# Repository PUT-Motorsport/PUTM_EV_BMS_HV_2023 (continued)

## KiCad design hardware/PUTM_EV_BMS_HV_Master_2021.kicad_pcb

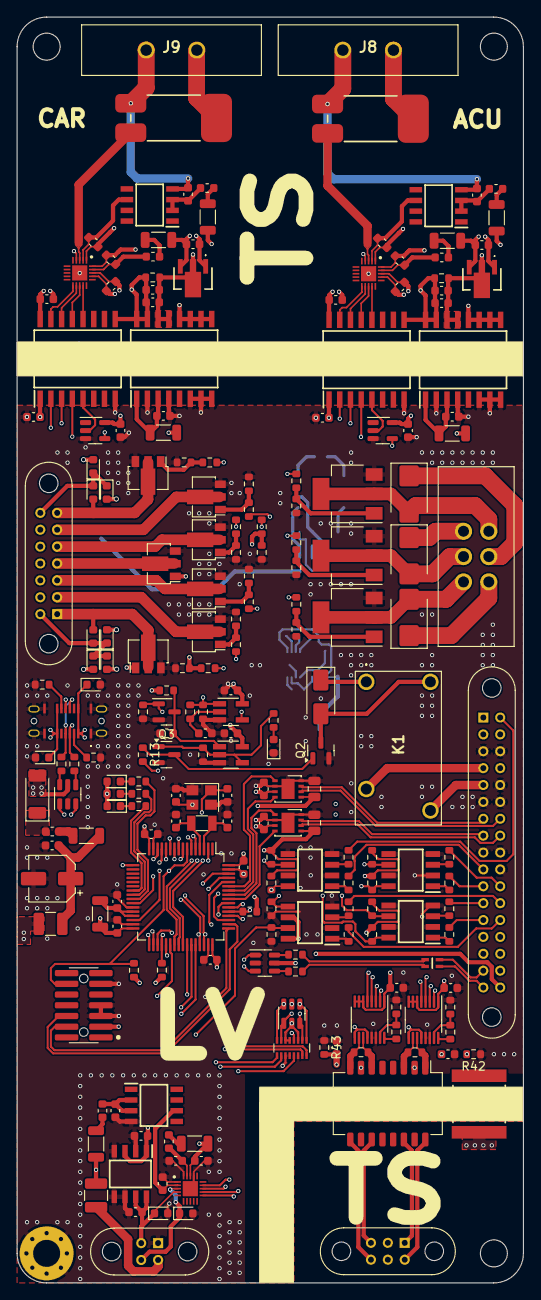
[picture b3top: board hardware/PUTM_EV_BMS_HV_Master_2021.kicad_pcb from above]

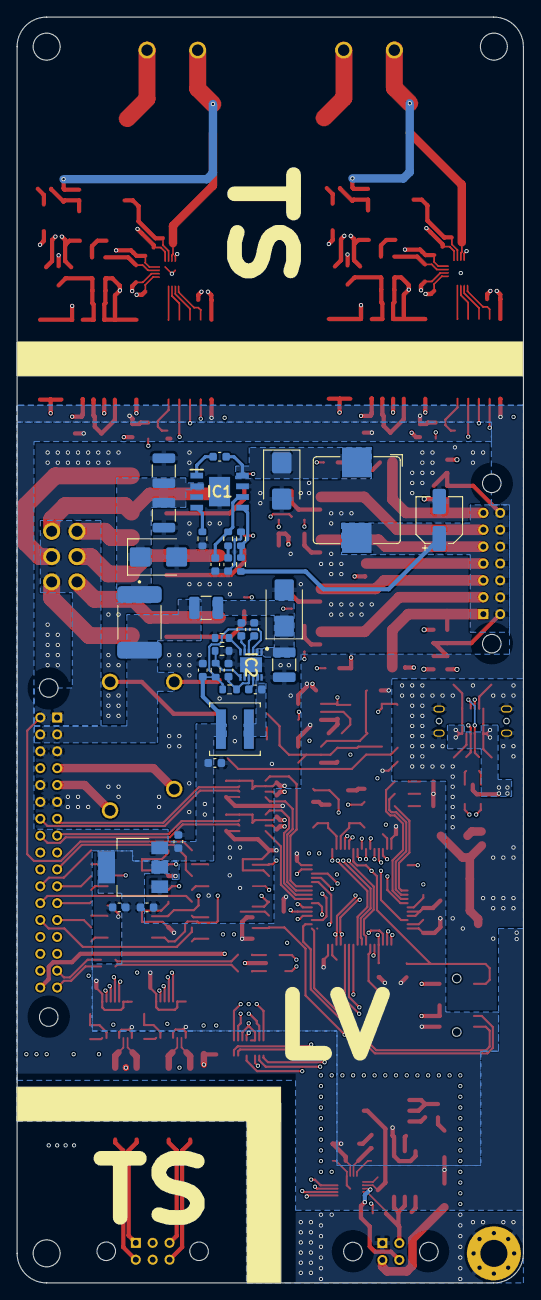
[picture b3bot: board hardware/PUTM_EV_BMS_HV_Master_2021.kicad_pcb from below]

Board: 4 copper layers, 60.0 x 150.0 mm, 253 parts (34 on the bottom side), 197 nets.

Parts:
C1, C2: 20pF; C_0603_1608Metric
C3, C4: 25pF; C_0603_1608Metric
C5, C6, C7, C8, C15, C16, C24, C25, C27, C28, C29, C33, C38, C39, C40, C42, C43, C46, C47, C49, C50, C52, C53, C56, C57, C58, C60, C61, C63, C64, C67, C68: 100nF; C_0603_1608Metric
C9, C10: 10uF/60V; C_1210_3225Metric
C11: 10pF; C_0603_1608Metric
C12: 12nF; C_0603_1608Metric
C13, C14: 1uF; C_0603_1608Metric
C17, C26: 100nF/60V; C_0603_1608Metric
C18: 100uF/12V; CP_Elec_5x4.5
C19: 47uF/12V; CP_Elec_5x4.5
C20: 2.2uF/60V; C_1210_3225Metric
C21: 5.6nF; C_0603_1608Metric
C22: 2.2uF; C_0603_1608Metric
C23, C41, C44, C51, C54, C55, C62, C65, C66: 10uF; C_0603_1608Metric
C30, C31: 47uF; C_0603_1608Metric
C32, C37: 100nF; C_0805_2012Metric
C34, C35: 22nF; C_0603_1608Metric
C36: 5.6nF/2000V; C2824
C45: 1nF; C_0603_1608Metric
C48, C59: 4.7uF; C_0603_1608Metric
D1, D2, D3, D8: SML-D12U1WT86; LED_0603_1608Metric
D4: SP0505BAHT; SOT-23-6
D5, D6, D17, D18, D19, D20, D21, D22, D23: CDBU0530; D_0603_1608Metric
D7: SS16-LTP; D_SMA
D9, D10, D15, D24: VSSB410S-E3/52T; D_SMB
D11, D16: SMBJ26CA-13-F; D_SMB
D12, D13: TSZU52C13; D_0603_1608Metric
D14: RB068LAM-30TFTR; D_SOD-128
F1, F3, F4: 0ZCH0050FF2G; Fuse_1210_3225Metric
F2: 576-2920L500/24SLDR; 2920L700SLPR
FB1, FB2, FB3, FB4, FB5, FB6, FB7: GZ1608D601TF; L_0603_1608Metric
FL1: DLW21SN501SK2L; DLW21SN121HQ2L
H1, H2, H4: M3; MountingHole_3.2mm_M3
H3: M3; MountingHole_3.2mm_M3_Pad_Via
IC1: RTQ2965GSP-QA; SOIC127P600X175-9N
IC2: MAX17643ATC+; SON50P300X300X80-13N
IC3: MCP3562T-E_NC; QFN40P300X300X60-21N-D
IC4: MCP1501-10E_SN; SOIC127P600X175-8N
IC5, IC10, IC16: REF193GSZ-REEL; SOIC127P600X175-8N
IC6, IC12: SN74LVC1G07DBVR; SOT-23-5
IC7, IC13: UCC12040DVE; SOIC127P1030X265-16N
IC8, IC14: ISO6763FDWR; SOIC127P1030X265-16N
IC9, IC15: AP7365-33YRG-13; AP736533YRG13
IC11, IC17: MCP3561T-E_NC; QFN40P300X300X60-21N-D
J1: M300-MV30645M1; M300MV30645M1
J2: M80-5103422; M80-51034YY
J3: M80-5100442; M80-51004YY
J4: FTSH-107-01-L-DV-K-A; FTSH-107-XX-YYY-DV-K-A
J5: M80-5101422; M80-51014YY
J6: USB4145-03-0070-C; USB4145030070C
J7: M80-5100622; M80-51006YY
J8, J9: M300-MV10345M1; M300MV10345M1
K1: 6-1419128-4; 614191284
L1, L3, L7, L10: 4.7uH; L_1206_3216Metric
L2: 33uH; L_Bourns_SRP1038C_10.0x10.0mm
L4: 10uH; L_Coilcraft_XAL5050-XXX
L5, L6, L8, L9, L11, L12: 1mH; L_1206_3216Metric
O1, O2, O3, O4: FOD8802DR2_IMG; SOIC127P600X175-8N
Q1, Q2, Q3: 2N7002; SOT-23
Q4, Q5, Q13: STN4NF06L; SOT-223-3_TabPin2
Q6, Q7, Q8, Q9, Q10, Q11, Q12: 2SK3065; SOT-89-3
R1, R2, R3, R5, R6, R15, R44, R45, R46, R47: 1k; R_0603_1608Metric
R4, R9, R11, R13, R14, R17, R19, R22, R23, R36, R37, R42, R43, R50, R51, R54, R55, R58, R59, R61, R64, R65, R67, R72, R73: 10k; R_0603_1608Metric
R7, R8: 5.1k; R_0603_1608Metric
R10: 100k; R_0603_1608Metric
R12: 1M; R_0603_1608Metric
R16, R18, R48, R49, R52, R53, R56, R57, R60, R66: 100R; R_0603_1608Metric
R20, R21, R34, R35, R62, R63, R70, R71: 2.7k; R_0603_1608Metric
R24: 20.5k; R_0603_1608Metric
R25: 392k; R_0603_1608Metric
R26: 147k; R_0603_1608Metric
R27: 10.5k; R_0603_1608Metric
R28: 40.2k; R_0603_1608Metric
R29: 4.7R; R_0603_1608Metric
R30: 105k; R_0603_1608Metric
R31: 23.2k; R_0603_1608Metric
R32, R33, R38, R39: 33R; R_0603_1608Metric
R40, R41: 120R; R_0603_1608Metric
R68, R69: 200R; R_0603_1608Metric
RD1, RD2: CDMM20M0F2500; CDMM
RN1: 33R; R_Array_Convex_8x0602
T1: HM1193NL; Transformer_Pulse_H1100NL
U1: STM32G484RETx; LQFP-64_10x10mm_P0.5mm
U2: 74LVC1G86; SOT-23-5_HandSoldering
U3: 74AUP1G32; SOT-23-5_HandSoldering
U4: LM1117-3.3; SOT-223-3_TabPin2
U5, U7: USBLC6-2SC6; SOT-23-6
U6, U8: MCP2542FD-E/MF; DFN-8-1EP_3x3mm_P0.65mm_EP1.55x2.4mm
U9, U10: LTC6820IMS; MSOP-16_3x4.039mm_P0.5mm
Y1: X322516MLB4SI; Crystal_SMD_3225-4Pin_3.2x2.5mm
Y2: Q13FC1350000400; Crystal_SMD_3215-2Pin_3.2x1.5mm

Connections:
+3.3VA: C23.1, L3.1, U1.28 (VREF+), U1.29 (VDDA)
+3V3: C6.2, C8.2, C14.1, C16.1, C24.1, C25.1, C28.1, C29.1, C32.2, C37.2, C39.1, C40.1, C42.1, C43.1, C47.1, C49.1, C58.1, C60.1, D1.2 (A), D2.2 (A), D3.2 (A), IC3.18 (DVDD), IC4.1 (VDD), IC4.3 (~SHDN), IC6.5, IC8.1 (VCC1), IC12.5, IC14.1 (VCC1), J4.3, L3.2, L5.1, O2.6, O2.8, R4.2, R5.2, R6.2, R12.1, R13.2, R22.2, R23.2, R64.2, R65.2, R72.2, R73.2, U1.16 (VDD), U1.32 (VDD), U1.48 (VDD), U1.64 (VDD), U2.5 (V), U3.5 (V), U4.2 (VO), U6.5 (VIO), U8.5 (VIO), U9.1 (EN), U9.6 (Vdds), U9.7 (POL), U9.8 (PHA), U9.9 (Vdd), U9.12 (MSTR), U10.1 (EN), U10.6 (Vdds), U10.7 (POL), U10.8 (PHA), U10.9 (Vdd), U10.12 (MSTR)
+5V: C13.1, C30.1, C31.1, C33.1, C38.1, F1.1, F3.1, IC2.3 (~RESET), L4.2, L6.1, L7.1, L10.1, R29.2, R30.2, U4.3 (VI), U6.3 (VDD), U8.3 (VDD)
+12V: C19.1, D17.1 (K), D18.1 (K), D19.1 (K), D20.1 (K), D21.1 (K), D22.1 (K), D23.1 (K), J5.8, J5.9, J5.10, J5.11, J5.12, J5.13, J5.14, L2.2, R26.2
/AIR_M_DETECT: O3.8, R64.1, U1.26 (PB2)
/AIR_PRE_DETECT: O3.6, R65.1, U1.17 (PA3)
/AIR_P_DETECT: O1.6, R23.1, U1.30 (PB10)
/AMS_FAULT_MCU: R9.2, R10.2, U1.51 (PA15), U2.1
/BOOT: O2.5, R36.2, U1.61 (PB8)
/CHARGER_DETECT: O4.8, R72.1, U1.62 (PB9)
/CLK_IN: C2.1, U1.5 (PF0), Y1.1
/CLK_OUT: C1.2, U1.6 (PF1), Y1.3
/Communication/LTC_1_I+: R40.2, T1.1, U9.11 (IP)
/Communication/LTC_1_I-: R40.1, T1.3, U9.10 (IM)
/Communication/LTC_1_OUT_I+: J7.4, T1.16
/Communication/LTC_1_OUT_I-: J7.1, T1.14
/Communication/LTC_2_I+: R41.2, T1.6, U10.11 (IP)
/Communication/LTC_2_I-: R41.1, T1.8, U10.10 (IM)
/Communication/LTC_2_OUT_I+: J7.3, T1.11
/Communication/LTC_2_OUT_I-: J7.6, T1.9
/Communication/LTC_CHASSIS: C36.2, J7.2, J7.5
/Connectors/MISO_C: D4.4 (K), J2.33, RN1.9 (R8.2)
/Connectors/MOSI_C: D4.3 (K), J2.32, RN1.10 (R7.2)
/Connectors/SCK_C: D4.5 (K), J2.31, RN1.12 (R5.2)
/Connectors/~EXT_CS_I_C: D4.6 (K), J2.14, RN1.16 (R1.2)
/Connectors/~EXT_CS_V_C: D4.1 (K), J2.15, RN1.15 (R2.2)
/FAN_1_CTRL: R48.2, U1.14 (PA2)
/FAN_2_CTRL: R52.2, U1.13 (PA1)
/FAN_3_CTRL: R56.2, U1.12 (PA0)
/FAN_4_CTRL: R60.2, U1.11 (PC3)
/FAN_5_CTRL: R49.2, U1.10 (PC2)
/FAN_6_CTRL: R53.2, U1.9 (PC1)
/FAN_7_CTRL: R57.2, U1.8 (PC0)
/IMD_SENS_PWM: O2.7, R37.1, U1.38 (PC6)
/LTC_1_~CS: U1.34 (PB12), U9.5 (~CS)
/LTC_2_~CS: U1.33 (PB11), U10.5 (~CS)
/LTC_MISO: R6.1, U1.36 (PB14), U9.3 (MISO), U10.3 (MISO)
/LTC_MOSI: U1.37 (PB15), U9.2 (MOSI), U10.2 (MOSI)
/LTC_SCK: U1.35 (PB13), U9.4 (SCK), U10.4 (SCK)
/MCU_CANFD1_RX: U1.58 (PB5), U8.4 (RXD)
/MCU_CANFD1_TX: U1.59 (PB6), U8.1 (TXD)
/MCU_CANFD2_RX: U1.56 (PB3), U6.4 (RXD)
/MCU_CANFD2_TX: U1.57 (PB4), U6.1 (TXD)
/MCU_D+: U1.46 (PA12), U5.3 (I/O2), U7.3 (I/O2)
/MCU_D-: U1.45 (PA11), U5.1 (I/O1), U7.1 (I/O1)
/MCU_LED_1: R3.1, U1.23 (PC5)
/MCU_LED_2: R2.1, U1.24 (PB0)
/MCU_LED_3: R1.1, U1.25 (PB1)
/Measurements/3V_REF: C46.2, IC3.2 (REFIN+), IC5.6 (REF_OUT)
/Measurements/Isolated acu measurement/3V_REF: C56.2, IC10.6 (REF_OUT), IC11.2 (REFIN+)
/Measurements/Isolated acu measurement/HV_+3.3V: C50.1, C53.1, C57.1, IC8.16 (VCC2), IC9.3 (VO), IC11.18 (DVDD), L9.1
/Measurements/Isolated acu measurement/HV_+5V: C51.1, C52.2, IC7.13 (SEL), IC7.14 (VISO), IC9.2 (VI), L8.1, R68.2
/Measurements/Isolated acu measurement/HV_GND: C50.2, C51.2, C52.1, C53.2, C54.2, C55.2, C56.1, C57.2, IC7.9 (GNDS), IC7.10 (NCS), IC7.11 (NCS), IC7.12 (NCS), IC7.15 (GNDS), IC7.16 (GNDS), IC8.9 (GND2), IC9.1 (GND), IC10.4 (GND), IC11.1 (REFIN-), IC11.4 (CH1), IC11.17 (DGND), IC11.20 (AGND), IC11.21 (EP), J8.1, R68.1, RD1.2
/Measurements/Isolated acu measurement/HV_MES+: IC11.3 (CH0), RD1.3
/Measurements/Isolated acu measurement/HV_SCK: IC8.14 (OUTB), IC11.12 (SCK)
/Measurements/Isolated acu measurement/HV_SDI: IC8.13 (OUTC), IC11.13 (SDI)
/Measurements/Isolated acu measurement/HV_SDO: IC8.12 (IND), IC11.14 (SDO)
/Measurements/Isolated acu measurement/HV_~CS: IC8.15 (OUTA), IC11.11 (~CS)
/Measurements/Isolated car measurement/3V_REF: C67.2, IC16.6 (REF_OUT), IC17.2 (REFIN+)
/Measurements/Isolated car measurement/HV_+3.3V: C61.1, C64.1, C68.1, IC14.16 (VCC2), IC15.3 (VO), IC17.18 (DVDD), L12.1
/Measurements/Isolated car measurement/HV_+5V: C62.1, C63.2, IC13.13 (SEL), IC13.14 (VISO), IC15.2 (VI), L11.1, R69.2
/Measurements/Isolated car measurement/HV_GND: C61.2, C62.2, C63.1, C64.2, C65.2, C66.2, C67.1, C68.2, IC13.9 (GNDS), IC13.10 (NCS), IC13.11 (NCS), IC13.12 (NCS), IC13.15 (GNDS), IC13.16 (GNDS), IC14.9 (GND2), IC15.1 (GND), IC16.4 (GND), IC17.1 (REFIN-), IC17.4 (CH1), IC17.17 (DGND), IC17.20 (AGND), IC17.21 (EP), J9.1, R69.1, RD2.2
/Measurements/Isolated car measurement/HV_MES+: IC17.3 (CH0), RD2.3
/Measurements/Isolated car measurement/HV_SCK: IC14.14 (OUTB), IC17.12 (SCK)
/Measurements/Isolated car measurement/HV_SDI: IC14.13 (OUTC), IC17.13 (SDI)
/Measurements/Isolated car measurement/HV_SDO: IC14.12 (IND), IC17.14 (SDO)
/Measurements/Isolated car measurement/HV_~CS: IC14.15 (OUTA), IC17.11 (~CS)
/Power/5V_SW: C20.1, D16.1 (K), F4.1, IC2.1 (VIN), IC2.2 (EN/UVLO)
/Power/12V_SW: C17.2, D15.1 (K), IC1.8 (SW), L2.1
/Power/12V_VIN: C9.1, C10.1, D11.1 (K), F2.1, IC1.2 (VIN)
/RTC_CLK_IN: C3.2, U1.3 (PC14), Y2.2
/RTC_CLK_OUT: C4.1, U1.4 (PC15), Y2.1
/SAFETY_DETECT: O4.6, R73.1, U1.2 (PC13)
/SIGNAL_AIR_M: R16.2, U1.41 (PC9)
/SIGNAL_AIR_P: R66.2, U1.40 (PC8)
/SIGNAL_AIR_PRE: R18.2, U1.39 (PC7)
/Safeties and related/AMS_FAULT: Q3.1 (G), R14.2, R15.1, U3.2, U3.4
/Safeties and related/AMS_FAULT_INTER: Q2.1 (G), Q3.3 (D), R13.1
/Safeties and related/CAP_VOLT: C7.2, Q1.3 (D), R12.2, U3.1
/Safeties and related/EDGE_DETECT: Q1.1 (G), R11.1, U2.4
/Safeties and related/IN_DELAY: C5.2, R10.1, U2.2
/Safeties and related/RELAY-: D7.2 (A), K1.4, Q2.3 (D)
/~MES_ACU_CS: IC8.2 (INA), U1.60 (PB7)
/~MES_CAR_CS: IC14.2 (INA), U1.55 (PD2)
/~SENS_CS: IC3.11 (~CS), U1.42 (PA8)
AIR_M-: D9.2 (A), J1.3, Q4.2 (D)
AIR_M_DETECTION: J2.13, R62.2
AIR_P-: D24.2 (A), J1.5, Q13.2 (D)
AIR_PRE-: D10.2 (A), J1.4, Q5.2 (D)
AIR_PRE_DETECTION: J2.12, R63.2
AIR_P_DETECTION: J2.28, R21.2
AMS_SAFETY_1: J2.4, K1.2
AMS_SAFETY_2: J2.5, K1.3
BOOT0: J2.29, R35.2
CANFD1+: J2.7, U8.7 (CANH)
CANFD1-: J2.24, U8.6 (CANL)
CANFD2+: J2.8, U6.7 (CANH)
CANFD2-: J2.25, U6.6 (CANL)
CHARGER_DETECTION: J2.10, R70.2
CUR_SENS_REF: C45.2, D5.1 (K), IC3.4 (CH1), IC4.7 (OUT), IC4.8 (FB), J3.2
CUR_SENS_SIG: D6.1 (K), IC3.3 (CH0), J3.4
D+: J6.A6 (D+), J6.B6 (D+), R32.2
D-: J6.A7 (D-), J6.B7 (D-), R33.1
EXT_RESET: J2.11, R20.2
EX_D+: FL1.4, J2.17
EX_D-: FL1.1, J2.16
EX_VBUS: J2.34, U7.5 (VBUS)
FAN1-: D17.2 (A), J5.1, Q6.2 (D)
FAN2-: D19.2 (A), J5.2, Q8.2 (D)
FAN3-: D21.2 (A), J5.3, Q10.2 (D)
FAN4-: D23.2 (A), J5.4, Q12.2 (D)
FAN5-: D18.2 (A), J5.5, Q7.2 (D)
FAN6-: D20.2 (A), J5.6, Q9.2 (D)
FAN7-: D22.2 (A), J5.7, Q11.2 (D)
GND: C1.1, C2.2, C3.1, C4.2, C5.1, C6.1, C7.1, C8.1, C9.2, C10.2, C11.2, C12.2, C13.2, C14.2, C15.2, C16.2, C18.2, C19.2, C20.2, C21.2, C22.2, C23.2, C24.2, C25.2, C27.2, C28.2, C29.2, C30.2, C31.2, C32.1, C33.2, C34.2, C35.2, C36.1, C37.1, C38.2, C39.2, C40.2, C41.2, C42.2, C43.2, C44.2, C45.1, C46.1, C47.2, C48.2, C49.2, C58.2, C59.2, C60.2, D4.2 (A), D5.2 (A), D6.2 (A), D8.1 (K), D11.2 (A), D12.2 (A), D13.2 (A), D15.2 (A), D16.2 (A), H3.1, IC1.7 (GND), IC1.9 (EP), IC2.8 (GND), IC2.12 (PGND), IC2.13 (EP), IC3.1 (REFIN-), IC3.17 (DGND), IC3.20 (AGND), IC3.21 (EP), IC4.2 (GND), IC4.4 (GND), IC4.5 (GND), IC4.6 (GND), IC5.4 (GND), IC6.3, IC7.2 (GNDP), IC7.4 (SYNC), IC7.6 (NC), IC7.7 (NC), IC7.8 (NC), IC8.8 (GND1), IC12.3, IC13.2 (GNDP), IC13.4 (SYNC), IC13.6 (NC), IC13.7 (NC), IC13.8 (NC), IC14.8 (GND1), J2.3, J2.6, J2.9, J2.20, J2.22, J2.23, J2.26, J2.27, J3.1, J4.5, J4.7, J4.11, J6.A1 (GND), J6.A12 (GND), J6.B1 (GND), J6.B12 (GND), J6.MH (SHIELD), O1.2, O1.4, O1.5, O1.7, O2.2, O2.4, O3.2, O3.4, O3.5, O3.7, O4.2, O4.4, O4.5, O4.7, Q1.2 (S), Q2.2 (S), Q3.2 (S), Q4.3 (S), Q5.3 (S), Q6.3 (S), Q7.3 (S), Q8.3 (S), Q9.3 (S), Q10.3 (S), Q11.3 (S), Q12.3 (S), Q13.3 (S), R7.2, R8.2, R9.1, R11.2, R14.1, R17.1, R19.1, R25.1, R27.1, R28.1, R31.1, R36.1, R37.2, R42.1, R43.1, R45.1, R47.1, R50.2, R51.2, R54.2, R55.2, R58.2, R59.2, R61.2, R67.1, RN1.3 (R3.1), RN1.4 (R4.1), RN1.6 (R6.1), RN1.11 (R6.2), RN1.13 (R4.2), RN1.14 (R3.2), U1.15 (VSS), U1.27 (VSSA), U1.31 (VSS), U1.47 (VSS), U1.63 (VSS), U2.3 (G), U3.3 (G), U4.1 (GND), U5.2 (GND), U6.2 (VSS), U6.8 (~STBY), U6.9 (VSS), U7.2 (GND), U8.2 (VSS), U8.8 (~STBY), U8.9 (VSS), U9.13 (SLOW), U9.14 (GND), U10.13 (SLOW), U10.14 (GND), Y1.2, Y1.4
IMD_SENSENSOR: J2.30, R34.2
MISO: IC3.14 (SDO), IC6.4, IC12.4, R5.1, RN1.8 (R8.1), U1.53 (PC11)
MOSI: IC3.13 (SDI), IC8.4 (INC), IC14.4 (INC), RN1.7 (R7.1), U1.54 (PC12)
NRST: J4.12, O1.8, R4.1, R22.1, U1.7 (PG10)
unnamed: C12.1, R24.1
unnamed: C15.1, C18.1, F3.2, L1.2
unnamed: C34.1, R42.2, T1.2
unnamed: C35.1, R43.2, T1.7
unnamed: D1.1 (K), R1.2
unnamed: D2.1 (K), R2.2
unnamed: D3.1 (K), R3.2
unnamed: D8.2 (A), R15.2
unnamed: D14.1 (K), FB1.2
unnamed: F1.2, J3.3
unnamed: FB1.1, L1.1
unnamed: FB2.1, L5.2
unnamed: FB3.1, L6.2
unnamed: FB4.1, L8.2
unnamed: FB5.1, L9.2
unnamed: FB6.1, L11.2
unnamed: FB7.1, L12.2
unnamed: FL1.2, R39.1
unnamed: FL1.3, R38.2
unnamed: C17.1, IC1.1 (BOOT)
unnamed: C11.1, IC1.6 (COMP), R24.2
unnamed: IC1.5 (FB), R26.1, R27.2
unnamed: IC1.4 (RT/SYNC), R25.2
unnamed: C26.1, IC2.10 (BST)
unnamed: C27.1, IC2.9 (EXTVCC), R29.1
unnamed: IC2.7 (FB), R30.1, R31.2
unnamed: C26.2, IC2.11 (LX), L4.1
unnamed: IC2.6 (RT/SYNC), R28.2
unnamed: C21.1, IC2.4 (SS)
unnamed: C22.1, IC2.5 (VCC)
unnamed: C41.1, FB2.2, IC3.19 (AVDD)
unnamed: C44.1, FB3.2, IC5.2 (VSS), IC5.3 (~SLEEP)
unnamed: C48.1, IC7.1 (EN), IC7.3 (VINP), L7.2
unnamed: IC6.2, IC8.5 (OUTD)
unnamed: C54.1, FB4.2, IC10.2 (VSS), IC10.3 (~SLEEP)
unnamed: C55.1, FB5.2, IC11.19 (AVDD)
unnamed: C59.1, IC13.1 (EN), IC13.3 (VINP), L10.2
unnamed: IC12.2, IC14.5 (OUTD)
unnamed: C65.1, FB6.2, IC16.2 (VSS), IC16.3 (~SLEEP)
unnamed: C66.1, FB7.2, IC17.19 (AVDD)
unnamed: J6.A5 (CC1), R8.1
unnamed: J6.B5 (CC2), R7.1
unnamed: J8.3, RD1.1
unnamed: J9.3, RD2.1
unnamed: O1.1, R20.1
unnamed: O1.3, R21.1
unnamed: O2.1, R34.1
unnamed: O2.3, R35.1
unnamed: O3.1, R62.1
unnamed: O3.3, R63.1
unnamed: O4.1, R70.1
unnamed: O4.3, R71.1
unnamed: Q4.1 (G), R16.1, R17.2
unnamed: Q5.1 (G), R18.1, R19.2
unnamed: Q6.1 (G), R48.1, R50.1
unnamed: Q7.1 (G), R49.1, R51.1
unnamed: Q8.1 (G), R52.1, R54.1
unnamed: Q9.1 (G), R53.1, R55.1
unnamed: Q10.1 (G), R56.1, R58.1
unnamed: Q11.1 (G), R57.1, R59.1
unnamed: Q12.1 (G), R60.1, R61.1
unnamed: Q13.1 (G), R66.1, R67.2
unnamed: R32.1, U5.4 (I/O2)
unnamed: R33.2, U5.6 (I/O1)
unnamed: R38.1, U7.4 (I/O2)
unnamed: R39.2, U7.6 (I/O1)
unnamed: R44.2, U9.16 (IBIAS)
unnamed: R44.1, R45.2, U9.15 (ICMP)
unnamed: R46.2, U10.16 (IBIAS)
unnamed: R46.1, R47.2, U10.15 (ICMP)
SAFETY_TSMS_IN: D9.1 (K), D10.1 (K), D24.1 (K), J1.1, J1.2, J1.6, J2.1, J2.18, R71.2
SCK: IC3.12 (SCK), IC8.3 (INB), IC14.3 (INB), RN1.5 (R5.1), U1.52 (PC10)
SWCLK: J4.6, U1.50 (PA14)
SWDIO: J4.4, U1.49 (PA13)
VBUS: D12.1 (K), D13.1 (K), D14.2 (A), J6.A4 (VBUS), J6.A9 (VBUS), J6.B4 (VBUS), J6.B9 (VBUS), U5.5 (VBUS)
VDD: D7.1 (K), F2.2, F4.2, J2.2, J2.19, K1.1
~EXT_CS_I: RN1.1 (R1.1), U1.44 (PA10)
~EXT_CS_V: RN1.2 (R2.1), U1.43 (PA9)

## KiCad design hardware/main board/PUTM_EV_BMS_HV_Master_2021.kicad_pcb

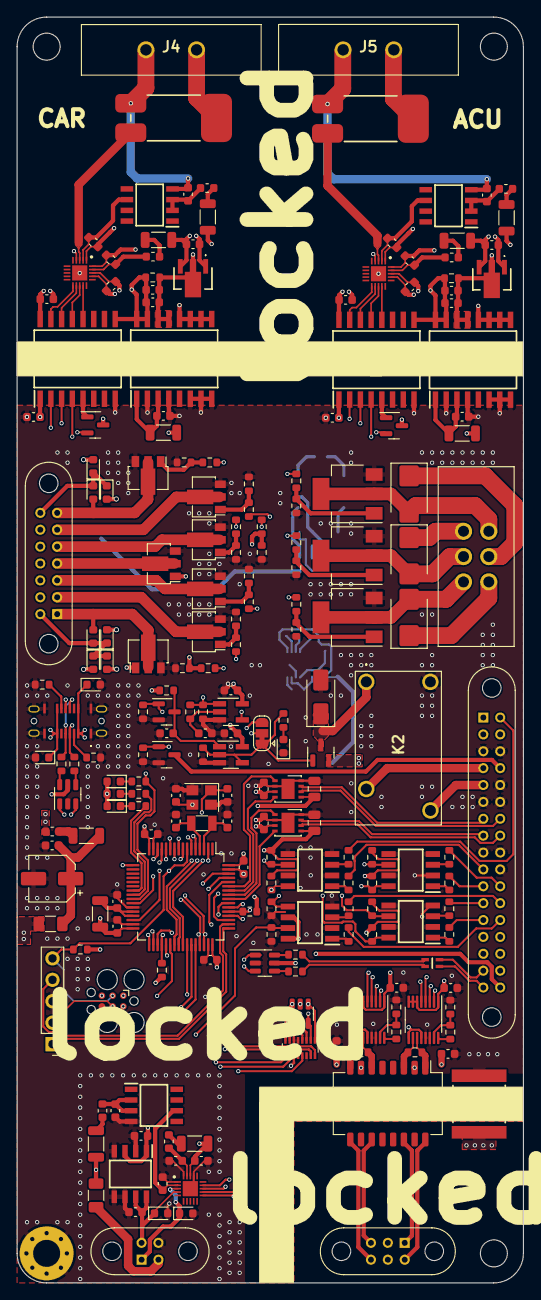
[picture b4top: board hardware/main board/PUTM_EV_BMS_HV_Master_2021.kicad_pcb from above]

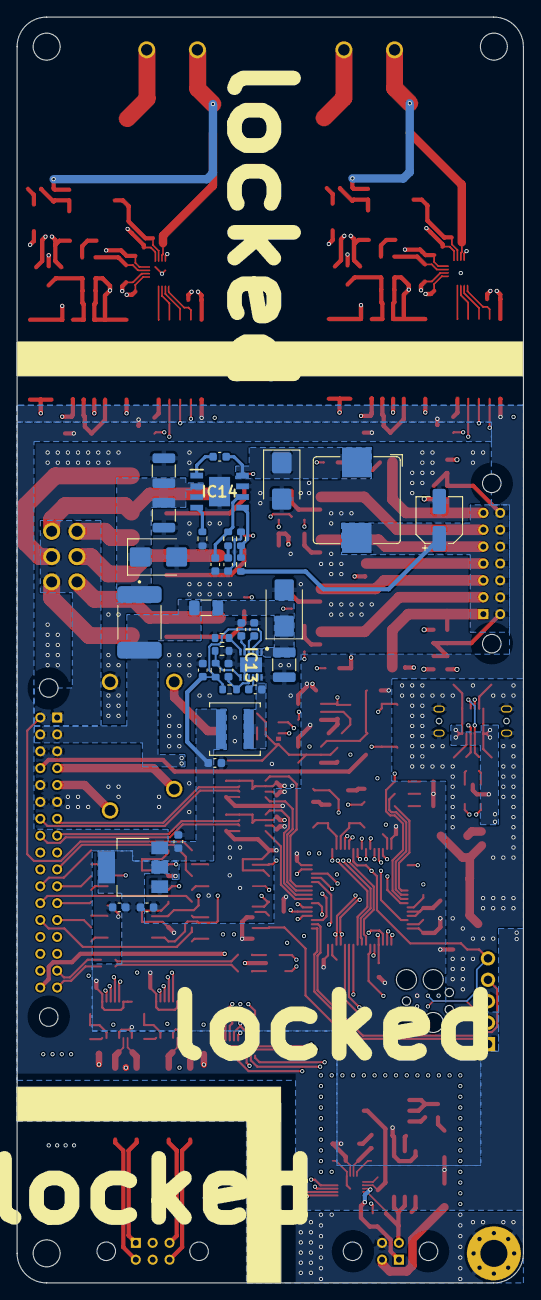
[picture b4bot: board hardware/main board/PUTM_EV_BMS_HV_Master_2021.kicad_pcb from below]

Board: 4 copper layers, 60.0 x 150.0 mm, 250 parts (34 on the bottom side), 197 nets.

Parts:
C1, C7, C9, C22, C26, C37, C46, C55, C56: 10uF; C_0603_1608Metric
C2, C4, C6, C13, C16, C17, C18, C19, C20, C23, C25, C30, C31, C32, C34, C35, C38, C39, C47, C50, C51, C52, C54, C57, C58, C59, C60, C63, C64, C66: 100nF; C_0603_1608Metric
C3, C11: 10uF/60V; C_1210_3225Metric
C5: 1nF; C_0603_1608Metric
C8, C68: 47uF; C_0603_1608Metric
C10, C21: 100nF; C_0805_2012Metric
C12, C15: 1uF; C_0603_1608Metric
C14: 100uF/12V; CP_Elec_5x4.5
C24: 2.2uF/60V; C_1210_3225Metric
C27: 5.6nF; C2824
C28, C29: 22nF; C_0603_1608Metric
C36, C49: 4.7uF; C_0603_1608Metric
C40, C41: 25pF; C_0603_1608Metric
C43, C44: 20pF; C_0603_1608Metric
C61: 12nF; C_0603_1608Metric
C62: 10pF; C_0603_1608Metric
C65, C71: 100nF/60V; C_0603_1608Metric
C67: 2.2uF; C_0603_1608Metric
C69: 5.6nF; C_0603_1608Metric
C72: 47uF/12V; CP_Elec_5x4.5
D1, D21, D22, D23: D_Zener_Small; D_0603_1608Metric
D2: 4A/80V; D_SMB
D3, D11: D_Zener_Small; D_SMB
D4, D12, D13: D_Small; D_SMB
D5, D6, D7, D9: LED_Small_ALT; LED_0603_1608Metric
D8: SP0505BAHT; SOT-23-6
D10: D_Small; D_SMA
D14, D15, D16, D17, D18, D19, D20: D_Schottky_Small; D_0603_1608Metric
F1: 0.5A; Fuse_1206_3216Metric
F2, F3: 1A; Fuse_1206_3216Metric
F4: 24V/5A; 2920L700SLPR
FB1, FB2, FB3, FB4, FB5, FB6, FB7: GZ1608D601TF; L_0603_1608Metric
FL1: DLW21SN501SK2L; DLW21SN121HQ2L
H1, H2, H4: M3; MountingHole_3.2mm_M3
H9: M3; MountingHole_3.2mm_M3_Pad_Via
IC1: MCP1501-10E_SN; SOIC127P600X175-8N
IC2, IC4: MCP3561T-E_NC; QFN40P300X300X60-21N-D
IC3, IC9, IC10: REF193GSZ-REEL; SOIC127P600X175-8N
IC6, IC11: AP7365-33YRG-13; AP736533YRG13
IC7: MCP3562T-E_NC; QFN40P300X300X60-21N-D
IC12, IC17: UCC12040DVE; SOIC127P1030X265-16N
IC13: MAX17643ATC+; SON50P300X300X80-13N
IC14: RTQ2965GSP-QA; SOIC127P600X175-9N
IC15, IC16: ISO6763FDWR; SOIC127P1030X265-16N
J1: USB4145-03-0070-C; USB4145030070C
J2: M80-5103422; M80-51034YY
J4, J5: M300-MV10345M1; M300MV10345M1
J6: M80-5100442; M80-51004YY
J9: M300-MV30645M1; M300MV30645M1
J10: M80-5100622; M80-51006YY
J11: M80-5101422; M80-51014YY
J14: Conn_01x05; PinHeader_1x05_P2.54mm_Vertical
J16: TagConnect; Tag-Connect_TC2030-IDC-FP_2x03_P1.27mm_Vertical
JP4: Cockpit; SolderJumper-3_P1.3mm_Bridged12_RoundedPad1.0x1.5mm
K2: 6-1419128-4; 614191284
L1, L2, L6, L7, L10, L12: LB3218T102K; L_1206_3216Metric
L3: 10uH; L_Bourns_SRP1038C_10.0x10.0mm
L4, L5, L8, L9: 6.8uH; L_1206_3216Metric
L11: 10uH; L_Coilcraft_XAL5050-XXX
O1, O2, O3, O5: FOD8802DR2_IMG; SOIC127P600X175-8N
Q1, Q7, Q9, Q12, Q13, Q14, Q15: 2SK3065; SOT-89-3
Q2, Q4, Q10, Q11: 2N7002; SOT-23
Q3, Q5, Q6: STN4NF06L; SOT-223-3_TabPin2
Q8: AO3400A; SOT-23
R1, R2, R3, R11, R15, R20, R21, R28, R29, R31, R33, R35, R39, R45, R46, R67: 10k; R_0603_1608Metric
R4, R6, R8, R10, R22, R30, R43, R47, R54, R56: 100R; R_0603_1608Metric
R5, R7, R9, R41, R48, R55, R60: 10K; R_0603_1608Metric
R12, R13, R14, R16, R24, R27, R40, R44: 2.7k; R_0603_1608Metric
R17: 4.7R; R_0603_1608Metric
R18, R19: 5.1k; R_0603_1608Metric
R23, R78: 200R; R_0603_1608Metric
R26, R36, R49, R50: 33R; R_0603_1608Metric
R32: 100k; R_0603_1608Metric
R34, R42, R69, R71, R72, R77: 1k; R_0603_1608Metric
R37, R53: 120R; R_0603_1608Metric
R38: 1M; R_0603_1608Metric
R51: 105k; R_0603_1608Metric
R52: 23.2k; R_0603_1608Metric
R57, R58, R62, R63: 1K; R_0603_1608Metric
R59: 40.2k; R_0603_1608Metric
R61: 20.5k; R_0603_1608Metric
R64: 392k; R_0603_1608Metric
R68: 147k; R_0603_1608Metric
R70: 10.5k; R_0603_1608Metric
RD1, RD2: CDMM20M0F2500; CDMM
RN2: 33; R_Array_Convex_8x0602
T1: HM1193NL; Transformer_Pulse_H1100NL
U1, U4: USBLC6-2SC6; SOT-23-6
U2: STM32G484RETx; LQFP-64_10x10mm_P0.5mm
U3, U6: MCP2542FDxMF; DFN-8-1EP_3x3mm_P0.65mm_EP1.55x2.4mm
U5: LM1117-3.3; SOT-223-3_TabPin2
U8: 74LVC1G86; SOT-23-5_HandSoldering
U12, U13: LTC6820IMS; MSOP-16_3x4.039mm_P0.5mm
U14: 74AUP1G32; SOT-23-5_HandSoldering
Y1: X322516MLB4SI; Crystal_SMD_3225-4Pin_3.2x2.5mm
Y2: Q13FC1350000400; Crystal_SMD_3215-2Pin_3.2x1.5mm

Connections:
+3.3VA: C55.1, L4.1, U2.28 (VREF+), U2.29 (VDDA)
+3V3: C2.1, C4.1, C10.2, C15.1, C16.1, C18.1, C21.2, C30.2, C32.1, C34.1, C35.1, C50.1, C51.1, C52.1, C54.1, C57.1, C60.1, C63.2, D5.2 (A), D6.2 (A), D7.2 (A), IC1.1 (VDD), IC1.3 (~SHDN), IC7.18 (DVDD), IC15.1 (VCC1), IC16.1 (VCC1), J14.1, J16.1 (VCC), L4.2, L6.1, O5.6, O5.8, Q10.3 (D), Q11.3 (D), R21.2, R29.2, R31.2, R33.2, R34.2, R35.2, R38.1, R42.2, R45.2, R67.2, U2.16 (VDD), U2.32 (VDD), U2.48 (VDD), U2.64 (VDD), U3.3 (VDD), U3.5 (VIO), U5.2 (VO), U6.3 (VDD), U6.5 (VIO), U8.5 (V), U12.1 (EN), U12.6 (Vdds), U12.7 (POL), U12.8 (PHA), U12.9 (Vdd), U12.12 (MSTR), U13.1 (EN), U13.6 (Vdds), U13.7 (POL), U13.8 (PHA), U13.9 (Vdd), U13.12 (MSTR), U14.5 (V)
+5V: C8.1, C12.1, C68.1, F1.1, F3.1, IC13.3 (~RESET), L1.1, L8.1, L9.1, L11.2, R17.2, R51.2, U5.3 (VI)
+12V: C72.1, D14.1 (K), D15.1 (K), D16.1 (K), D17.1 (K), D18.1 (K), D19.1 (K), D20.1 (K), J11.8, J11.9, J11.10, J11.11, J11.12, J11.13, J11.14, L3.2, R68.2
/AIR_M_DETECT: O3.8, R29.1, U2.26 (PB2)
/AIR_PRE_DETECT: O3.6, R35.1, U2.17 (PA3)
/AIR_P_DETECT: O1.6, R33.1, U2.30 (PB10)
/AMS_FAULT_MCU: R1.2, R32.2, U2.51 (PA15), U8.1
/BOOT: O5.5, R20.2, U2.61 (PB8)
/CHARGER_DETECT: O2.6, R45.1, U2.2 (PC13)
/CLK_IN: C44.1, U2.5 (PF0), Y1.1
/CLK_OUT: C43.2, U2.6 (PF1), Y1.3
/Connectors/LTC_1_OUT_I+: J10.4, T1.16
/Connectors/LTC_1_OUT_I-: J10.1, T1.14
/Connectors/LTC_2_OUT_I+: J10.3, T1.11
/Connectors/LTC_2_OUT_I-: J10.6, T1.9
/Connectors/LTC_CHASSIS: C27.2, J10.2, J10.5
/Connectors/MISO_C: D8.4 (K), J2.33, RN2.9 (R8.2)
/Connectors/MOSI_C: D8.3 (K), J2.32, RN2.10 (R7.2)
/Connectors/SCK_C: D8.5 (K), J2.31, RN2.12 (R5.2)
/Connectors/~EXT_CS_I_C: D8.6 (K), J2.14, RN2.16 (R1.2)
/Connectors/~EXT_CS_V_C: D8.1 (K), J2.15, RN2.15 (R2.2)
/FAN_1_CTRL: R4.2, U2.14 (PA2)
/FAN_2_CTRL: R6.2, U2.13 (PA1)
/FAN_3_CTRL: R8.2, U2.12 (PA0)
/FAN_4_CTRL: R10.2, U2.11 (PC3)
/FAN_5_CTRL: R47.2, U2.10 (PC2)
/FAN_6_CTRL: R54.2, U2.9 (PC1)
/FAN_7_CTRL: R56.2, U2.8 (PC0)
/IMD_SENS_PWM: O5.7, R15.1, U2.38 (PC6)
/LTC_1_~CS: U2.34 (PB12), U12.5 (~CS)
/LTC_2_~CS: U2.33 (PB11), U13.5 (~CS)
/LTC_MISO: R42.1, U2.36 (PB14), U12.3 (MISO), U13.3 (MISO)
/LTC_MOSI: U2.37 (PB15), U12.2 (MOSI), U13.2 (MOSI)
/LTC_SCK: U2.35 (PB13), U12.4 (SCK), U13.4 (SCK)
/MCU_CANFD1_RX: U2.58 (PB5), U6.4 (RXD)
/MCU_CANFD1_TX: U2.59 (PB6), U6.1 (TXD)
/MCU_CANFD2_RX: U2.56 (PB3), U3.4 (RXD)
/MCU_CANFD2_TX: U2.57 (PB4), U3.1 (TXD)
/MCU_D+: U1.3 (I/O2), U2.46 (PA12), U4.3 (I/O2)
/MCU_D-: U1.1 (I/O1), U2.45 (PA11), U4.1 (I/O1)
/MCU_LED_1: R69.1, U2.23 (PC5)
/MCU_LED_2: R71.1, U2.24 (PB0)
/MCU_LED_3: JP4.3 (B), R72.1, U2.25 (PB1)
/Measurements/3V_REF: C6.2, IC3.6 (REF_OUT), IC7.2 (REFIN+)
/Measurements/Isolated acu measurement/3V_REF: C20.2, IC2.2 (REFIN+), IC9.6 (REF_OUT)
/Measurements/Isolated acu measurement/HV_+3.3V: C13.1, C17.1, C39.1, IC2.18 (DVDD), IC6.3 (VO), IC15.16 (VCC2), L10.1
/Measurements/Isolated acu measurement/HV_+5V: C37.1, C38.2, IC6.2 (VI), IC12.13 (SEL), IC12.14 (VISO), L2.1, R23.2
/Measurements/Isolated acu measurement/HV_MES+: IC2.3 (CH0), RD1.3
/Measurements/Isolated acu measurement/HV_SCK: IC2.12 (SCK), IC15.14 (OUTB)
/Measurements/Isolated acu measurement/HV_SDI: IC2.13 (SDI), IC15.13 (OUTC)
/Measurements/Isolated acu measurement/HV_SDO: IC2.14 (SDO), IC15.12 (IND)
/Measurements/Isolated acu measurement/HV_~CS: IC2.11 (~CS), IC15.15 (OUTA)
/Measurements/Isolated car measurement/3V_REF: C47.2, IC4.2 (REFIN+), IC10.6 (REF_OUT)
/Measurements/Isolated car measurement/HV_+3.3V: C23.1, C31.1, C59.1, IC4.18 (DVDD), IC11.3 (VO), IC16.16 (VCC2), L12.1
/Measurements/Isolated car measurement/HV_+5V: C56.1, C58.2, IC11.2 (VI), IC17.13 (SEL), IC17.14 (VISO), L7.1, R78.2
/Measurements/Isolated car measurement/HV_MES+: IC4.3 (CH0), RD2.3
/Measurements/Isolated car measurement/HV_SCK: IC4.12 (SCK), IC16.14 (OUTB)
/Measurements/Isolated car measurement/HV_SDI: IC4.13 (SDI), IC16.13 (OUTC)
/Measurements/Isolated car measurement/HV_SDO: IC4.14 (SDO), IC16.12 (IND)
/Measurements/Isolated car measurement/HV_~CS: IC4.11 (~CS), IC16.15 (OUTA)
/RTC_CLK_IN: C40.2, U2.3 (PC14), Y2.2
/RTC_CLK_OUT: C41.1, U2.4 (PC15), Y2.1
/SAFETY_DETECT: O2.8, R67.1, U2.62 (PB9)
/SIGNAL_AIR_M: R22.2, U2.41 (PC9)
/SIGNAL_AIR_P: R43.2, U2.40 (PC8)
/SIGNAL_AIR_PRE: R30.2, U2.39 (PC7)
/Safeties and related/AMS_FAULT: JP4.1 (A), Q8.1 (G), R11.2, R77.1, U14.2, U14.4
/Safeties and related/CAP_VOLT: C25.2, Q2.3 (D), R38.2, U14.1
/Safeties and related/EDGE_DETECT: Q2.1 (G), R3.1, U8.4
/Safeties and related/IN_DELAY: C64.2, R32.1, U8.2
/~MES_ACU_CS: IC15.2 (INA), U2.60 (PB7)
/~MES_CAR_CS: IC16.2 (INA), U2.55 (PD2)
/~SENS_CS: IC7.11 (~CS), U2.42 (PA8)
AIR_M-: D4.2 (A), J9.3, Q3.2 (D)
AIR_M_DETECTION: J2.13, R24.2
AIR_P-: D13.2 (A), J9.5, Q6.2 (D)
AIR_PRE-: D12.2 (A), J9.4, Q5.2 (D)
AIR_PRE_DETECTION: J2.12, R27.2
AIR_P_DETECTION: J2.28, R16.2
AMS_FAULT_COCKPIT: J2.21, Q4.3 (D)
AMS_SAFETY_1: J2.4, K2.2
AMS_SAFETY_2: J2.5, K2.3
BOOT0: J2.29, R13.2
CANFD1+: J2.7, U6.7 (CANH)
CANFD1-: J2.24, U6.6 (CANL)
CANFD2+: J2.8, U3.7 (CANH)
CANFD2-: J2.25, U3.6 (CANL)
CHARGER_DETECTION: J2.10, R40.2
CUR_SENS_REF: C5.2, D23.1 (K), IC1.7 (OUT), IC1.8 (FB), IC7.4 (CH1), J6.3
CUR_SENS_SIG: D22.1 (K), IC7.3 (CH0), J6.1
D+: J1.A6 (D+), J1.B6 (D+), R49.2
D-: J1.A7 (D-), J1.B7 (D-), R50.1
EXT_RESET: J2.11, R14.2
EX_D+: FL1.4, J2.17
EX_D-: FL1.1, J2.16
EX_VBUS: J2.34, U1.5 (VBUS)
FAN1-: D15.2 (A), J11.1, Q1.2 (D)
FAN2-: D14.2 (A), J11.2, Q7.2 (D)
FAN3-: D16.2 (A), J11.3, Q9.2 (D)
FAN4-: D17.2 (A), J11.4, Q12.2 (D)
FAN5-: D20.2 (A), J11.5, Q13.2 (D)
FAN6-: D19.2 (A), J11.6, Q14.2 (D)
FAN7-: D18.2 (A), J11.7, Q15.2 (D)
GND: C1.2, C2.2, C3.2, C4.2, C5.1, C6.1, C8.2, C10.1, C11.2, C12.2, C14.2, C15.2, C16.2, C18.2, C19.2, C21.1, C24.2, C25.1, C26.2, C27.1, C28.2, C29.2, C30.1, C32.2, C34.2, C35.2, C36.2, C40.1, C41.2, C43.1, C44.2, C49.2, C50.2, C51.2, C52.2, C54.2, C55.2, C57.2, C60.2, C61.2, C62.2, C63.1, C64.1, C66.2, C67.2, C68.2, C69.2, C72.2, D1.2 (A), D2.2 (A), D3.2 (A), D8.2 (A), D9.1 (K), D10.2 (A), D11.2 (A), D21.2 (A), D22.2 (A), D23.2 (A), H9.1, IC1.2 (GND), IC1.4 (GND), IC1.5 (GND), IC1.6 (GND), IC3.4 (GND), IC7.1 (REFIN-), IC7.17 (DGND), IC7.20 (AGND), IC7.21 (EP), IC12.2 (GNDP), IC12.4 (SYNC), IC12.6 (NC), IC12.7 (NC), IC12.8 (NC), IC13.8 (GND), IC13.12 (PGND), IC13.13 (EP), IC14.7 (GND), IC14.9 (EP), IC15.8 (GND1), IC16.8 (GND1), IC17.2 (GNDP), IC17.4 (SYNC), IC17.6 (NC), IC17.7 (NC), IC17.8 (NC), J1.A1 (GND), J1.A12 (GND), J1.B1 (GND), J1.B12 (GND), J1.MH (SHIELD), J2.3, J2.6, J2.9, J2.20, J2.22, J2.23, J2.26, J2.27, J6.4, J14.3, J16.5 (GND), K2.4, O1.2, O1.4, O1.5, O1.7, O2.2, O2.4, O2.5, O2.7, O3.2, O3.4, O3.5, O3.7, O5.2, O5.4, Q1.3 (S), Q2.2 (S), Q3.3 (S), Q4.2 (S), Q5.3 (S), Q6.3 (S), Q7.3 (S), Q9.3 (S), Q12.3 (S), Q13.3 (S), Q14.3 (S), Q15.3 (S), R1.1, R2.2, R3.2, R5.2, R7.2, R9.2, R11.1, R15.2, R18.2, R19.2, R20.1, R28.1, R39.1, R41.2, R46.1, R48.2, R52.1, R55.2, R59.1, R60.2, R62.1, R63.1, R64.1, R70.1, RN2.3 (R3.1), RN2.4 (R4.1), RN2.6 (R6.1), RN2.11 (R6.2), RN2.13 (R4.2), RN2.14 (R3.2), U1.2 (GND), U2.15 (VSS), U2.27 (VSSA), U2.31 (VSS), U2.47 (VSS), U2.63 (VSS), U3.2 (VSS), U3.8 (~STBY), U3.9 (VSS), U4.2 (GND), U5.1 (GND), U6.2 (VSS), U6.8 (~STBY), U6.9 (VSS), U8.3 (G), U12.13 (SLOW), U12.14 (GND), U13.13 (SLOW), U13.14 (GND), U14.3 (G), Y1.2, Y1.4
HV_ACU+: J5.3, RD1.1
HV_ACU-: C7.2, C9.2, C13.2, C17.2, C20.1, C37.2, C38.1, C39.2, IC2.1 (REFIN-), IC2.4 (CH1), IC2.17 (DGND), IC2.20 (AGND), IC2.21 (EP), IC6.1 (GND), IC9.4 (GND), IC12.9 (GNDS), IC12.10 (NCS), IC12.11 (NCS), IC12.12 (NCS), IC12.15 (GNDS), IC12.16 (GNDS), IC15.9 (GND2), J5.1, R23.1, RD1.2
HV_CAR+: J4.3, RD2.1
HV_CAR-: C22.2, C23.2, C31.2, C46.2, C47.1, C56.2, C58.1, C59.2, IC4.1 (REFIN-), IC4.4 (CH1), IC4.17 (DGND), IC4.20 (AGND), IC4.21 (EP), IC10.4 (GND), IC11.1 (GND), IC16.9 (GND2), IC17.9 (GNDS), IC17.10 (NCS), IC17.11 (NCS), IC17.12 (NCS), IC17.15 (GNDS), IC17.16 (GNDS), J4.1, R78.1, RD2.2
IMD_SENSENSOR: J2.30, R12.2
LTC_1_I+: R53.2, T1.1, U12.11 (IP)
LTC_1_I-: R53.1, T1.3, U12.10 (IM)
LTC_2_I+: R37.2, T1.6, U13.11 (IP)
LTC_2_I-: R37.1, T1.8, U13.10 (IM)
MISO: IC7.14 (SDO), Q10.2 (S), Q11.2 (S), R34.1, RN2.8 (R8.1), U2.53 (PC11)
MOSI: IC7.13 (SDI), IC15.4 (INC), IC16.4 (INC), RN2.7 (R7.1), U2.54 (PC12)
NRST: J14.5, J16.3 (~RESET), O1.8, R21.1, R31.1, U2.7 (PG10)
unnamed: C14.1, C19.1, F3.2, L5.2
unnamed: C28.1, T1.2
unnamed: C29.1, T1.7
unnamed: C61.1, R61.1
unnamed: C71.2, D2.1 (K), IC14.8 (SW), L3.1
unnamed: C3.1, C11.1, D3.1 (K), F4.1, IC14.2 (VIN)
unnamed: D5.1 (K), R69.2
unnamed: D6.1 (K), R71.2
unnamed: D7.1 (K), R72.2
unnamed: D9.2 (A), R77.2
unnamed: D10.1 (K), K2.1, Q8.3 (D)
unnamed: C24.1, D11.1 (K), F2.1, IC13.1 (VIN), IC13.2 (EN/UVLO)
unnamed: F1.2, J6.2
unnamed: FB1.1, L5.1
unnamed: FB2.1, L2.2
unnamed: FB3.1, L7.2
unnamed: FB4.1, L10.2
unnamed: FB5.1, L12.2
unnamed: FB6.1, L6.2
unnamed: FB7.1, L1.2
unnamed: FL1.2, R36.1
unnamed: FL1.3, R26.2
unnamed: C7.1, FB4.2, IC2.19 (AVDD)
unnamed: C1.1, FB7.2, IC3.2 (VSS), IC3.3 (~SLEEP)
unnamed: C22.1, FB5.2, IC4.19 (AVDD)
unnamed: C26.1, FB6.2, IC7.19 (AVDD)
unnamed: C9.1, FB2.2, IC9.2 (VSS), IC9.3 (~SLEEP)
unnamed: C46.1, FB3.2, IC10.2 (VSS), IC10.3 (~SLEEP)
unnamed: C36.1, IC12.1 (EN), IC12.3 (VINP), L8.2
unnamed: C65.1, IC13.10 (BST)
unnamed: C66.1, IC13.9 (EXTVCC), R17.1
unnamed: IC13.7 (FB), R51.1, R52.2
unnamed: C65.2, IC13.11 (LX), L11.1
unnamed: IC13.6 (RT/SYNC), R59.2
unnamed: C69.1, IC13.4 (SS)
unnamed: C67.1, IC13.5 (VCC)
unnamed: C71.1, IC14.1 (BOOT)
unnamed: C62.1, IC14.6 (COMP), R61.2
unnamed: IC14.5 (FB), R68.1, R70.2
unnamed: IC14.4 (RT/SYNC), R64.2
unnamed: IC15.5 (OUTD), Q10.1 (G)
unnamed: IC16.5 (OUTD), Q11.1 (G)
unnamed: C49.1, IC17.1 (EN), IC17.3 (VINP), L9.2
unnamed: J1.A5 (CC1), R18.1
unnamed: J1.B5 (CC2), R19.1
unnamed: JP4.2 (C), Q4.1 (G), R2.1
unnamed: O1.1, R14.1
unnamed: O1.3, R16.1
unnamed: O2.1, R40.1
unnamed: O2.3, R44.1
unnamed: O3.1, R24.1
unnamed: O3.3, R27.1
unnamed: O5.1, R12.1
unnamed: O5.3, R13.1
unnamed: Q1.1 (G), R4.1, R5.1
unnamed: Q3.1 (G), R22.1, R28.2
unnamed: Q5.1 (G), R30.1, R39.2
unnamed: Q6.1 (G), R43.1, R46.2
unnamed: Q7.1 (G), R6.1, R7.1
unnamed: Q9.1 (G), R8.1, R9.1
unnamed: Q12.1 (G), R10.1, R41.1
unnamed: Q13.1 (G), R47.1, R48.1
unnamed: Q14.1 (G), R54.1, R55.1
unnamed: Q15.1 (G), R56.1, R60.1
unnamed: R26.1, U1.4 (I/O2)
unnamed: R36.2, U1.6 (I/O1)
unnamed: R49.1, U4.4 (I/O2)
unnamed: R50.2, U4.6 (I/O1)
unnamed: R57.2, U12.16 (IBIAS)
unnamed: R57.1, R62.2, U12.15 (ICMP)
unnamed: R58.2, U13.16 (IBIAS)
unnamed: R58.1, R63.2, U13.15 (ICMP)
SAFETY_TSMS_IN: D4.1 (K), D12.1 (K), D13.1 (K), J2.1, J2.18, J9.1, J9.2, J9.6, R44.2
SCK: IC7.12 (SCK), IC15.3 (INB), IC16.3 (INB), RN2.5 (R5.1), U2.52 (PC10)
SWCLK: J14.2, J16.4 (SWCLK), U2.50 (PA14)
SWDIO: J14.4, J16.2 (SWDIO), U2.49 (PA13)
VBUS: D1.1 (K), D21.1 (K), FB1.2, J1.A4 (VBUS), J1.A9 (VBUS), J1.B4 (VBUS), J1.B9 (VBUS), U4.5 (VBUS)
VDD: F2.2, F4.2, J2.2, J2.19, Q8.2 (S)
~EXT_CS_I: RN2.1 (R1.1), U2.44 (PA10)
~EXT_CS_V: RN2.2 (R2.1), U2.43 (PA9)

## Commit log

2022-10-05 .gitingore update
2022-10-09 moved safety, connectors and ext mem to new sheets
2022-10-10 finished remaking whole schematic
2022-10-10 finished remaking the schematic
2022-10-11 added external firmware to repo, add usb connector (molex 4pin 90deg) on schematic
2022-10-11 added additional USB port and overall board update
2022-10-11 sync, cuz not much was changed
2022-10-11 switched all screw terminals for corresponding molexes n-pins 90 deg
2022-10-18 fixed HV measurement
2022-10-18 minor changes
2022-10-24 changed the logic behind the error latch circuit and added some 3d models for used harwin connectors
2022-10-25 added discharge resistor to latch circuit
2022-10-25 some visual changes
2022-10-26 changed d flip flop to a or gate based latch
2022-11-08 erased all traces, finished USB section, started HV section, swapped most footprints of R to be of the same type 0603 similary with caps (where it could be done), swapped optos for those used in Smar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
2022-11-08 finished HV section
2022-11-08 minor HV section change
2022-11-08 HV section fix - forgot about capacitors
2022-11-08 3d models update, more work on pcb
2022-11-08 Schematic readability update
2022-11-08 sync
2022-11-09 finished pcb layout, started routing, changed 2 layered board to 4 layered'
2022-11-11 finished board design
2022-11-11 resized board and added some visual info
2022-11-11 added missing led for safety indication
2022-11-11 remade pcb so it fits into 100 x 100 mm and some minor modifications
2022-11-14 schematic override, just cuz
2022-11-14 pcb sync, half the new new new layout is done
2022-11-22 changed HV measurements from isolated opamp to isolated ADC with isolated spi communication, changed safety laatching from mosfet back to relay
2022-11-25 changed the 1V voltage ref made from RL circuit to low noise, 0.1% error 1.024 V ref gen, and changed the opamp used for current sensor feedback filtration to a high precision low drift opamp
2022-11-29 pcb update
2022-12-06 schemat sync
2022-12-11 board sync and measurments section adjustments
2022-12-13 measurments section changes, sorted components on the board into groups, changed main connector and added seprate for AIRs, added IMD PWM input as well as AIR fault detection
2022-12-14 hv elem positioning update'
2022-12-15 changed few connectors, finished board HV section and other minor changes
2022-12-16 board sync
2023-01-10 pcb iter 4?
2023-01-10 drawings update
2023-01-14 ground plane fix
2023-01-16 board layout changes, moved USB from seprate connector to the main connector, moved optos to the bootom right corner, moved IMD signal and air detection to a seprate connector
2023-05-02 remake in progress
2023-05-04 bigger board, distinct HV/LV and isolation, some schematic changes
2023-05-09 major changes: conn, fans, inputs and others
2023-05-09 further improvements
2023-05-11 PCB routing 50-70% done
2023-05-12 done
2023-05-15 production fiels update
2023-05-15 slight change to one of the fill zones and added gerbers/and bom to the git files
2023-05-15 slight changes and adjustments to 12V power section
2023-05-17 WęGoRz AfTeR rEvIeW cOmMiT
2023-05-17 via-s stormed the capitalgit status!
2023-05-17 Logo + designer
2023-06-25 poprawka schematu dziwny bug z gerberami/kicadem przy wylewaniu tego samego neta z różnymi priorytetami i zmiana r_array z 5 (bo takich nie da się kupić XD na 8
2023-07-20 added LTC lib insitu
2023-07-20 fixed work folder
2023-07-20 working commit
2023-07-22 LTC manager & controller update
2023-07-22 spidmacontroller update, ltc manager update
2023-07-22 Charger ready to test.
2023-07-22 further work on ltc manager
2023-07-22 removed can lib files
2023-07-22 Added can as submodule
2023-07-22 Added can start
2023-07-25 ltc controller update, board update
2023-07-25 Revert "further work on ltc manager"
    This reverts commit b7f355d2cc7a36195d8f9671f446215ee6a9210d.
2023-07-30 SpiController redesign & LtcContoller optimazation, deleted CAN lib copy, added concepts for most templates
2023-07-30 merged charger branch
2023-08-02 MCP356 lib expansion
2023-08-03 resolve compile errors
2023-08-03 Added AIR State Machine diagram
2023-08-03 Added CAN car
2023-08-03 ltc ctrl update
2023-08-03 ltc controller update
2023-08-03 Can car sending cell voltage data
2023-08-03 Update can car
2023-08-03 hardware update - fixed pcb errors
2023-08-04 moved config to seprate file
2023-08-04 Fix can error, added error checker draft
2023-08-04 Basic Error checking ready to test.
2023-08-04 Works as expected
2023-08-04 ltc controller fix
2023-08-04 ltc update
2023-08-04 balance draft
2023-08-04 mcp356 controller fix
2023-08-04 didn't do shit
2023-08-04 renames
2023-08-05 lib include clean up
2023-08-05 clean up
2023-08-05 code review and clean up
2023-08-05 mcp update & clean up
2023-08-05 ltc & mcp clean up & optimazation
2023-08-05 ltc clean up & optimazation
2023-08-05 cocepts update
2023-08-05 mcp356x clean up
2023-08-07 schematic clean up
2023-08-07 mcp356x update
2023-08-08 mcp working
2023-08-10 Turn on the AMS Fault after 2 sec
2023-08-10 New toolchain fix
2023-08-10 AIR SM
2023-08-13 AIR sm development
2023-08-15 Working AIR SM, current sensor calibration, and v car valibration
2023-08-15 can update
2023-08-16 working CAN
2023-08-17 Add print to the console
2023-08-17 update StackData
2023-08-18 Create JSON, Send JSON via USB
2023-08-18 Lock mock values
2023-08-18 added soc
2023-08-18 charger update
2023-08-19 Working charger
2023-08-19 Working usb one way communication
2023-08-20 added temperature calculation
2023-08-22 Fix temperature calc
2023-08-22 Added all checks
2023-08-22 pre test
2023-08-22 Ready for tests
2023-08-25 working AMS cocpit indicator
2023-08-26 post tests
2023-08-26 temp cal
2023-08-26 send avg soc
2023-08-27 soc fix
2023-09-21 updated components to comply with new resolutions
2023-09-21 HV car mes layout
2023-09-25 components layout
2023-10-02 syncing branches
2023-10-02 smaller board layout proposition
2023-10-02 step + rounded pcb corners
2023-10-09 done power plane layout
2023-10-24 repairing demaged branch~
2023-11-14 slight changes, changed shield's coupling resitor to a couplingcapacitor
2023-11-14 erased symbold and values on pcb
2023-11-24 production version
2023-11-24 lck delete
2023-12-26 step file erase
2024-01-03 moved hardware/main_board to hardware, deleted hardware/main_baord and hardware/connector_board, changed highside driveing transistors in acu and car HV mes to a open drain buffer for clarity and les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
2024-01-03 pcb slight touches
2024-01-05 schmall update
2024-02-23 symbol update
2024-06-04 relay new driving logic, some ltc communication changes
2024-06-30 vsv ready
2024-07-15 new hardware
2024-07-23 major schematic changes
2024-07-24 fixed some footprints; shorted pcb board to 60x100; re-designed the HV & current measuring as well as LTC communication, all are in one TS section;
2024-07-24 new beginings tbc
2024-07-25 changes tbc
2024-07-30 schematic done
2024-08-02 new firmware for bga version of stm, change stm from smt to bga, smaller HV dividers, added 3rd can transciver, and other
2024-08-04 mcu pinout done
2024-08-08 firmware, clean up
2024-08-12 FSG CHANGES, state: - added min precharge time, - air state machine remade, - acu voltage measurement and current sense working, - all slaves working, - usb / app working
2024-08-12 fast commit;
2024-08-14 fsg sym
2024-08-17 added todo
2024-08-20 Update README.md
    readme mid update :3
2024-08-20 Update README.md
    readme updateto
2024-08-20 Update README.md
    readmememememem
2024-08-24 before fsp for WEGORZ
2024-08-24 submodule change
2024-08-24 json fix part 1
2024-08-24 json fix part 2
2024-08-27 fsp sync
2024-09-01 mama comit
2024-09-28 inductors 3d models fix, smaller relay (same series as the one from IMD), other + sync
2024-10-22 all but the communications sections done
2024-10-24 idk probably working
2024-12-05 the connectors wil stay and wont be changed further
2024-12-05 LV section component placement done
2024-12-07 some routing done
2024-12-07 layotu done, some more routing done
2024-12-07 some more routing done & HV section routing done
2024-12-09 routing done, drc checked
2024-12-09 some after touchups
2024-12-09 qfn mcu instead of bga sadge ;-;
2024-12-09 added version, pcb name, logo and initials
2024-12-10 changing mcu done + new routing
2024-12-11 sync;
2024-12-11 sync, layout done, now its time for the routing
2024-12-13 this is it i can tell this is the end
2024-12-14 last fix
2024-12-15 bom update
2025-01-12 moved old firmware to tmp folder, created new stm32 project for new firmware, fixed 3.3V pd in the pcb project
2025-01-17 data
2025-01-19 docs matlab update
2025-01-19 bode_wave commit
2025-01-25 sdc current data
2025-01-25 some error changes
2025-01-25 sdc current daa
2025-01-25 matlab calc update
2025-01-25 dcnev250 current data
2025-02-08 timers test code + setup
2025-02-12 adc reg structs implement
2025-02-17 some more program done
2025-02-18 adc some more code done
